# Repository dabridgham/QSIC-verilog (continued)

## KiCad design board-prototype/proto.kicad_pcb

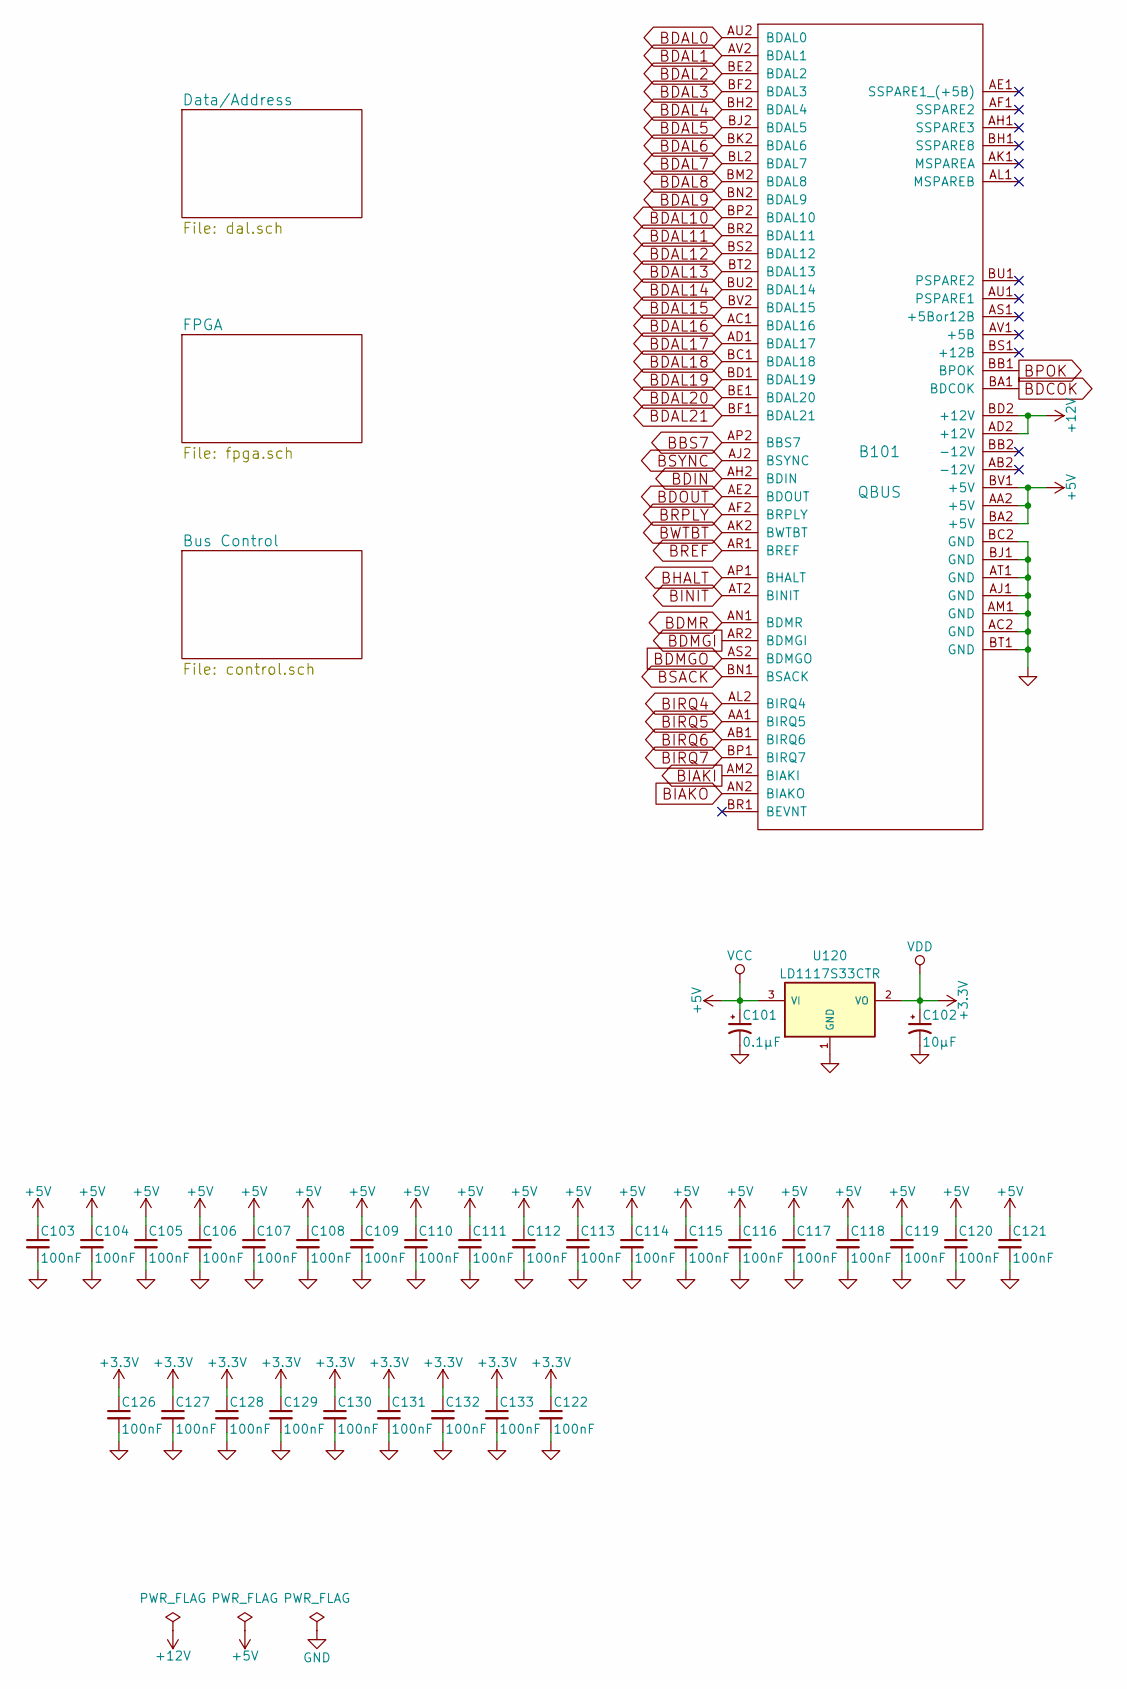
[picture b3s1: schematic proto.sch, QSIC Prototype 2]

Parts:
B101: QBUS; Qbus-double
C101: 0.1µF; TantalC_SizeR_EIA-2012
C102: 10µF; TantalC_SizeR_EIA-2012
C103, C104, C105, C106, C107, C108, C109, C110, C111, C112, C113, C114, C115, C116, C117, C118, C119, C120, C121, C122, C126, C127, C128, C129, C130, C131, C132, C133: 100nF; C_0805
U120: LD1117S33CTR; SOT-223

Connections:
+5V: B101.AA2 (+5V), B101.BA2 (+5V), B101.BV1 (+5V), C101.1, C103.1, C104.1, C105.1, C106.1, C107.1, C108.1, C109.1, C110.1, C111.1, C112.1, C113.1, C114.1, C115.1, C116.1, C117.1, C118.1, C119.1, C120.1, C121.1, U120.3 (VI); also elsewhere on the board
+12V: B101.AD2 (+12V), B101.BD2 (+12V); also elsewhere on the board
BBS7: B101.AP2 (BBS7); also elsewhere on the board
BDAL0: B101.AU2 (BDAL0); also elsewhere on the board
BDAL1: B101.AV2 (BDAL1); also elsewhere on the board
BDAL2: B101.BE2 (BDAL2); also elsewhere on the board
BDAL3: B101.BF2 (BDAL3); also elsewhere on the board
BDAL4: B101.BH2 (BDAL4); also elsewhere on the board
BDAL5: B101.BJ2 (BDAL5); also elsewhere on the board
BDAL6: B101.BK2 (BDAL6); also elsewhere on the board
BDAL7: B101.BL2 (BDAL7); also elsewhere on the board
BDAL8: B101.BM2 (BDAL8); also elsewhere on the board
BDAL9: B101.BN2 (BDAL9); also elsewhere on the board
BDAL10: B101.BP2 (BDAL10); also elsewhere on the board
BDAL11: B101.BR2 (BDAL11); also elsewhere on the board
BDAL12: B101.BS2 (BDAL12); also elsewhere on the board
BDAL13: B101.BT2 (BDAL13); also elsewhere on the board
BDAL14: B101.BU2 (BDAL14); also elsewhere on the board
BDAL15: B101.BV2 (BDAL15); also elsewhere on the board
BDAL16: B101.AC1 (BDAL16); also elsewhere on the board
BDAL17: B101.AD1 (BDAL17); also elsewhere on the board
BDAL18: B101.BC1 (BDAL18); also elsewhere on the board
BDAL19: B101.BD1 (BDAL19); also elsewhere on the board
BDAL20: B101.BE1 (BDAL20); also elsewhere on the board
BDAL21: B101.BF1 (BDAL21); also elsewhere on the board
BDCOK: B101.BA1 (BDCOK); also elsewhere on the board
BDIN: B101.AH2 (BDIN); also elsewhere on the board
BDMGI: B101.AR2 (BDMGI); also elsewhere on the board
BDMGO: B101.AS2 (BDMGO); also elsewhere on the board
BDMR: B101.AN1 (BDMR); also elsewhere on the board
BDOUT: B101.AE2 (BDOUT); also elsewhere on the board
BHALT: B101.AP1 (BHALT); also elsewhere on the board
BIAKI: B101.AM2 (BIAKI); also elsewhere on the board
BIAKO: B101.AN2 (BIAKO); also elsewhere on the board
BINIT: B101.AT2 (BINIT); also elsewhere on the board
BIRQ4: B101.AL2 (BIRQ4); also elsewhere on the board
BIRQ5: B101.AA1 (BIRQ5); also elsewhere on the board
BIRQ6: B101.AB1 (BIRQ6); also elsewhere on the board
BIRQ7: B101.BP1 (BIRQ7); also elsewhere on the board
BPOK: B101.BB1 (BPOK); also elsewhere on the board
BREF: B101.AR1 (BREF); also elsewhere on the board
BRPLY: B101.AF2 (BRPLY); also elsewhere on the board
BSACK: B101.BN1 (BSACK); also elsewhere on the board
BSYNC: B101.AJ2 (BSYNC); also elsewhere on the board
BWTBT: B101.AK2 (BWTBT); also elsewhere on the board

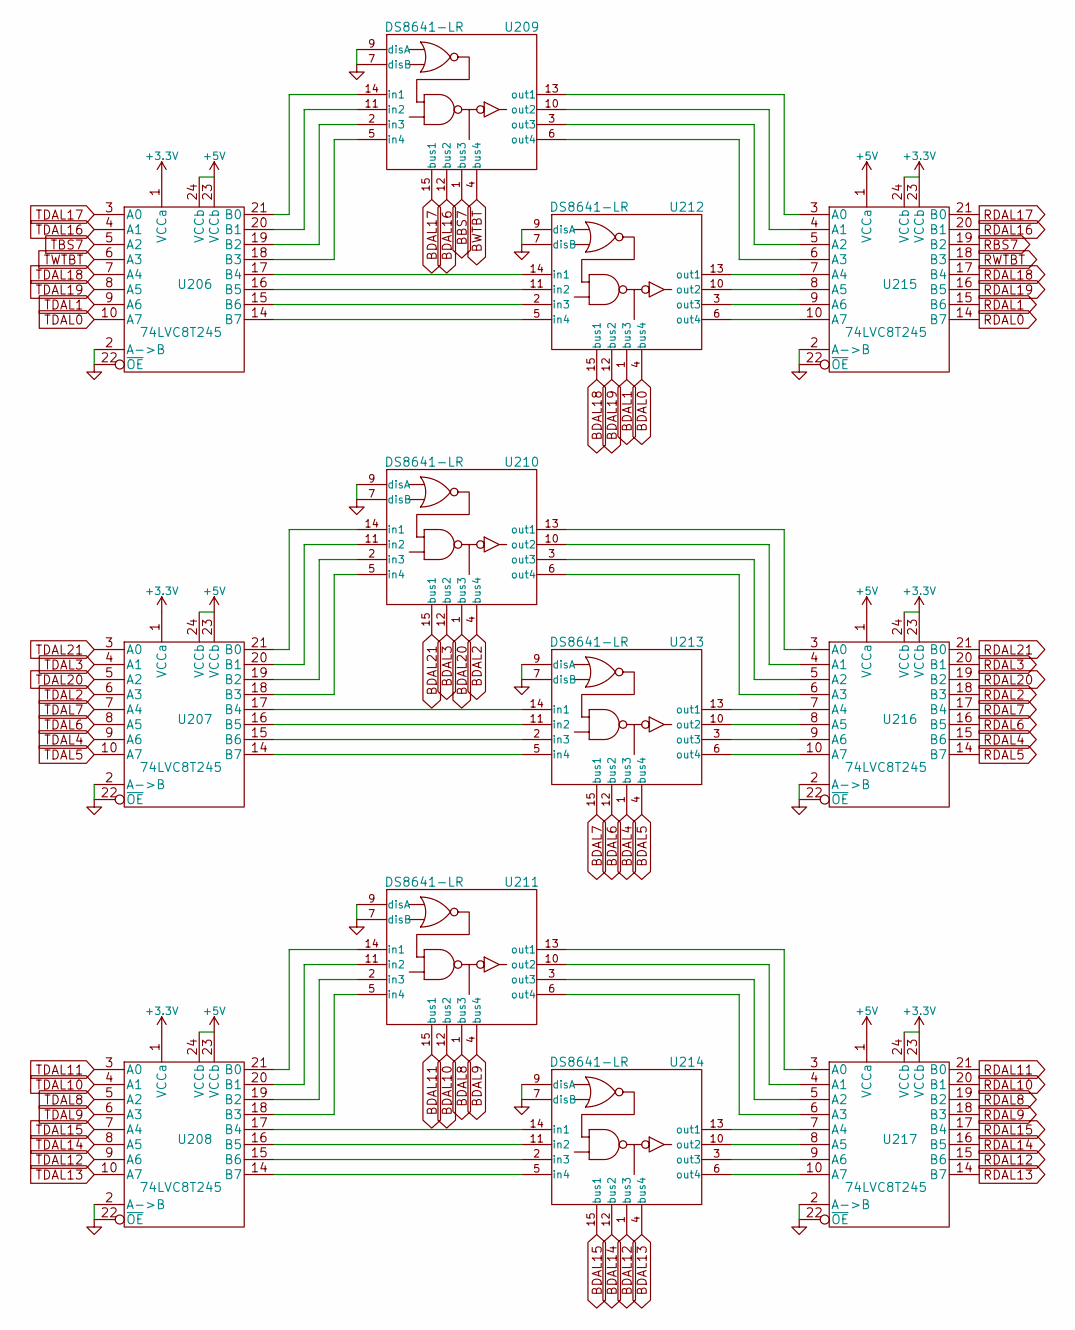
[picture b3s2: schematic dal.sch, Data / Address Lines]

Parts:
U206, U207, U208, U215, U216, U217: 74LVC8T245; TSSOP-24_4.4x7.8mm_Pitch0.65mm
U209, U210, U211, U212, U213, U214: DS8641-LR; DIP-16__300

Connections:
+5V: U206.23 (VCCb), U206.24 (VCCb), U207.23 (VCCb), U207.24 (VCCb), U208.23 (VCCb), U208.24 (VCCb), U209.16 (VCC), U210.16 (VCC), U211.16 (VCC), U212.16 (VCC), U213.16 (VCC), U214.16 (VCC), U215.1 (VCCa), U216.1 (VCCa), U217.1 (VCCa); also elsewhere on the board
BBS7: U209.1 (bus3); also elsewhere on the board
BDAL0: U212.4 (bus4); also elsewhere on the board
BDAL1: U212.1 (bus3); also elsewhere on the board
BDAL2: U210.4 (bus4); also elsewhere on the board
BDAL3: U210.12 (bus2); also elsewhere on the board
BDAL4: U213.1 (bus3); also elsewhere on the board
BDAL5: U213.4 (bus4); also elsewhere on the board
BDAL6: U213.12 (bus2); also elsewhere on the board
BDAL7: U213.15 (bus1); also elsewhere on the board
BDAL8: U211.1 (bus3); also elsewhere on the board
BDAL9: U211.4 (bus4); also elsewhere on the board
BDAL10: U211.12 (bus2); also elsewhere on the board
BDAL11: U211.15 (bus1); also elsewhere on the board
BDAL12: U214.1 (bus3); also elsewhere on the board
BDAL13: U214.4 (bus4); also elsewhere on the board
BDAL14: U214.12 (bus2); also elsewhere on the board
BDAL15: U214.15 (bus1); also elsewhere on the board
BDAL16: U209.12 (bus2); also elsewhere on the board
BDAL17: U209.15 (bus1); also elsewhere on the board
BDAL18: U212.15 (bus1); also elsewhere on the board
BDAL19: U212.12 (bus2); also elsewhere on the board
BDAL20: U210.1 (bus3); also elsewhere on the board
BDAL21: U210.15 (bus1); also elsewhere on the board
BWTBT: U209.4 (bus4); also elsewhere on the board
unnamed: U206.14 (B7), U212.5 (in4)
unnamed: U206.15 (B6), U212.2 (in3)
unnamed: U206.16 (B5), U212.11 (in2)
unnamed: U206.17 (B4), U212.14 (in1)
unnamed: U206.18 (B3), U209.5 (in4)
unnamed: U206.19 (B2), U209.2 (in3)
unnamed: U206.20 (B1), U209.11 (in2)
unnamed: U206.21 (B0), U209.14 (in1)
unnamed: U207.14 (B7), U213.5 (in4)
unnamed: U207.15 (B6), U213.2 (in3)
unnamed: U207.16 (B5), U213.11 (in2)
unnamed: U207.17 (B4), U213.14 (in1)
unnamed: U207.18 (B3), U210.5 (in4)
unnamed: U207.19 (B2), U210.2 (in3)
unnamed: U207.20 (B1), U210.11 (in2)
unnamed: U207.21 (B0), U210.14 (in1)
unnamed: U208.14 (B7), U214.5 (in4)
unnamed: U208.15 (B6), U214.2 (in3)
unnamed: U208.16 (B5), U214.11 (in2)
unnamed: U208.17 (B4), U214.14 (in1)
unnamed: U208.18 (B3), U211.5 (in4)
unnamed: U208.19 (B2), U211.2 (in3)
unnamed: U208.20 (B1), U211.11 (in2)
unnamed: U208.21 (B0), U211.14 (in1)
unnamed: U209.3 (out3), U215.5 (A2)
unnamed: U209.6 (out4), U215.6 (A3)
unnamed: U209.10 (out2), U215.4 (A1)
unnamed: U209.13 (out1), U215.3 (A0)
unnamed: U210.3 (out3), U216.5 (A2)
unnamed: U210.6 (out4), U216.6 (A3)
unnamed: U210.10 (out2), U216.4 (A1)
unnamed: U210.13 (out1), U216.3 (A0)
unnamed: U211.3 (out3), U217.5 (A2)
unnamed: U211.6 (out4), U217.6 (A3)
unnamed: U211.10 (out2), U217.4 (A1)
unnamed: U211.13 (out1), U217.3 (A0)
unnamed: U212.3 (out3), U215.9 (A6)
unnamed: U212.6 (out4), U215.10 (A7)
unnamed: U212.10 (out2), U215.8 (A5)
unnamed: U212.13 (out1), U215.7 (A4)
unnamed: U213.3 (out3), U216.9 (A6)
unnamed: U213.6 (out4), U216.10 (A7)
unnamed: U213.10 (out2), U216.8 (A5)
unnamed: U213.13 (out1), U216.7 (A4)
unnamed: U214.3 (out3), U217.9 (A6)
unnamed: U214.6 (out4), U217.10 (A7)
unnamed: U214.10 (out2), U217.8 (A5)
unnamed: U214.13 (out1), U217.7 (A4)
RBS7: U215.19 (B2); also elsewhere on the board
RDAL0: U215.14 (B7); also elsewhere on the board
RDAL1: U215.15 (B6); also elsewhere on the board
RDAL2: U216.18 (B3); also elsewhere on the board
RDAL3: U216.20 (B1); also elsewhere on the board
RDAL4: U216.15 (B6); also elsewhere on the board
RDAL5: U216.14 (B7); also elsewhere on the board
RDAL6: U216.16 (B5); also elsewhere on the board
RDAL7: U216.17 (B4); also elsewhere on the board
RDAL8: U217.19 (B2); also elsewhere on the board
RDAL9: U217.18 (B3); also elsewhere on the board
RDAL10: U217.20 (B1); also elsewhere on the board
RDAL11: U217.21 (B0); also elsewhere on the board
RDAL12: U217.15 (B6); also elsewhere on the board
RDAL13: U217.14 (B7); also elsewhere on the board
RDAL14: U217.16 (B5); also elsewhere on the board
RDAL15: U217.17 (B4); also elsewhere on the board
RDAL16: U215.20 (B1); also elsewhere on the board
RDAL17: U215.21 (B0); also elsewhere on the board
RDAL18: U215.17 (B4); also elsewhere on the board
RDAL19: U215.16 (B5); also elsewhere on the board
RDAL20: U216.19 (B2); also elsewhere on the board
RDAL21: U216.21 (B0); also elsewhere on the board
RWTBT: U215.18 (B3); also elsewhere on the board
TBS7: U206.5 (A2); also elsewhere on the board
TDAL0: U206.10 (A7); also elsewhere on the board
TDAL1: U206.9 (A6); also elsewhere on the board
TDAL2: U207.6 (A3); also elsewhere on the board
TDAL3: U207.4 (A1); also elsewhere on the board
TDAL4: U207.9 (A6); also elsewhere on the board
TDAL5: U207.10 (A7); also elsewhere on the board
TDAL6: U207.8 (A5); also elsewhere on the board
TDAL7: U207.7 (A4); also elsewhere on the board
TDAL8: U208.5 (A2); also elsewhere on the board
TDAL9: U208.6 (A3); also elsewhere on the board
TDAL10: U208.4 (A1); also elsewhere on the board
TDAL11: U208.3 (A0); also elsewhere on the board
TDAL12: U208.9 (A6); also elsewhere on the board
TDAL13: U208.10 (A7); also elsewhere on the board
TDAL14: U208.8 (A5); also elsewhere on the board
TDAL15: U208.7 (A4); also elsewhere on the board
TDAL16: U206.4 (A1); also elsewhere on the board
TDAL17: U206.3 (A0); also elsewhere on the board
TDAL18: U206.7 (A4); also elsewhere on the board
TDAL19: U206.8 (A5); also elsewhere on the board
TDAL20: U207.5 (A2); also elsewhere on the board
TDAL21: U207.3 (A0); also elsewhere on the board
TWTBT: U206.6 (A3); also elsewhere on the board

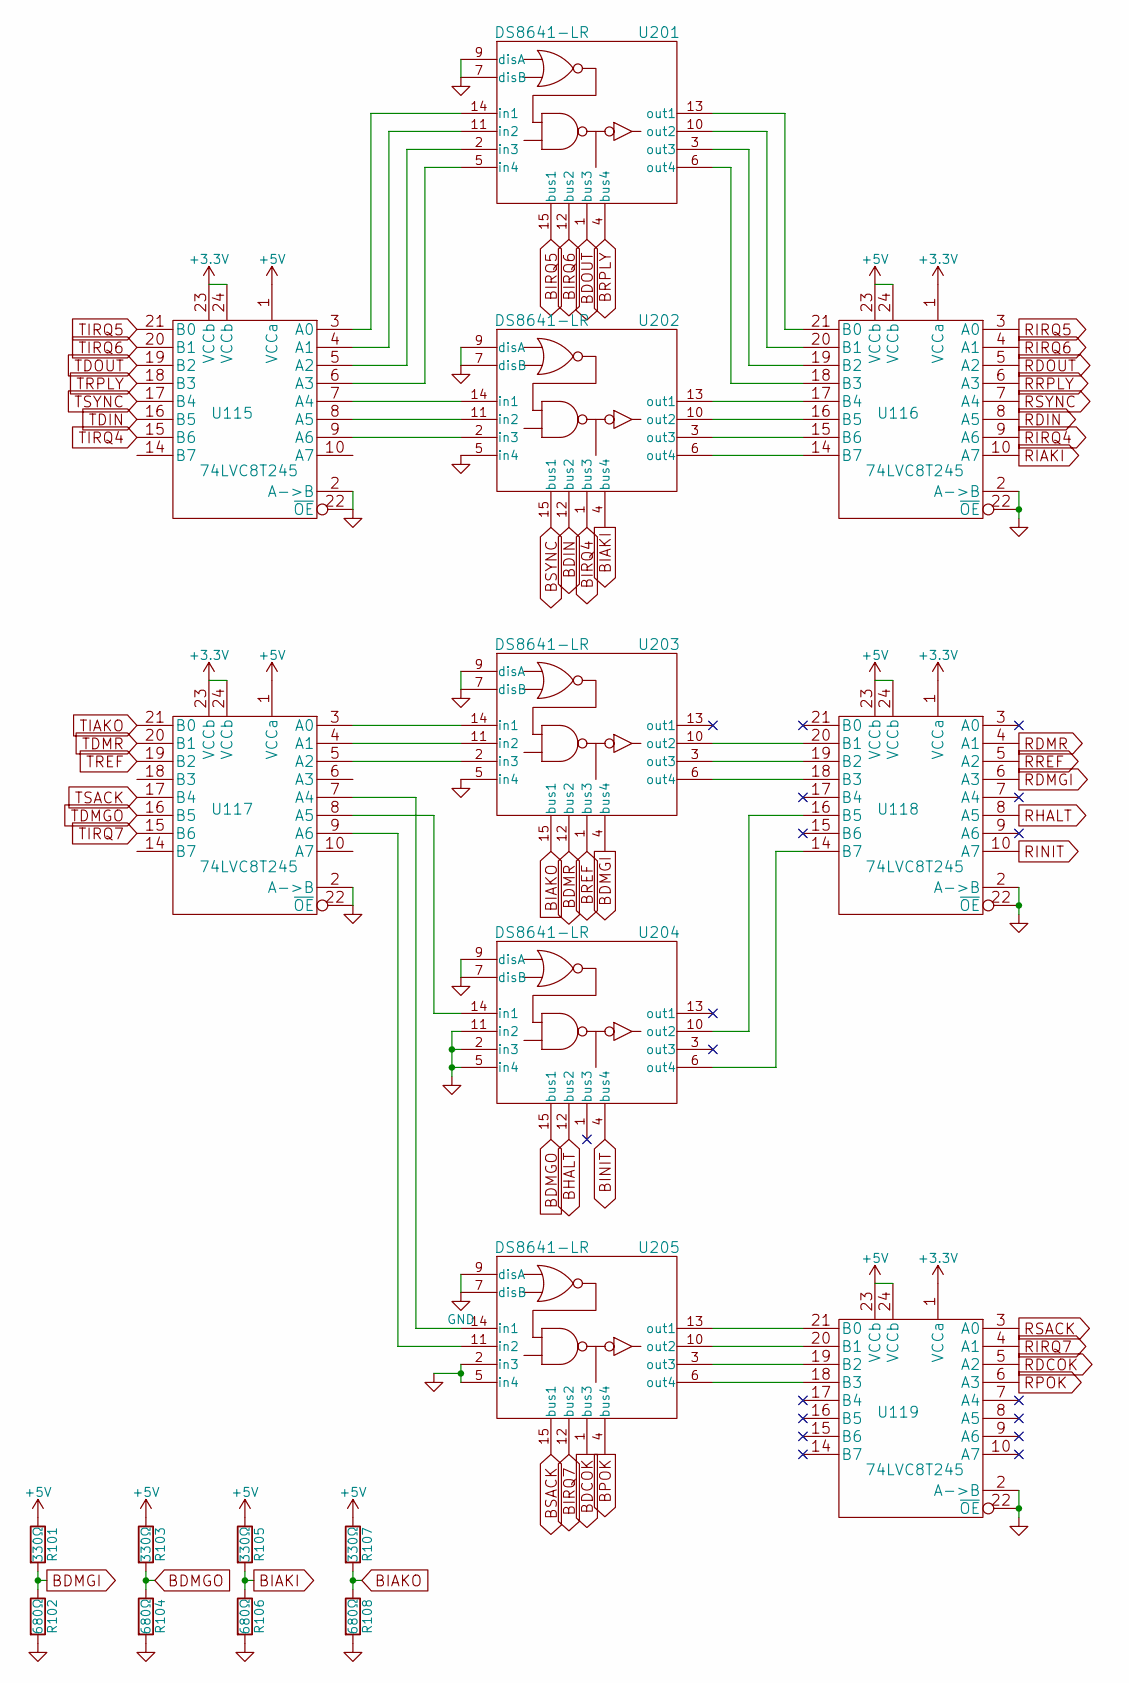
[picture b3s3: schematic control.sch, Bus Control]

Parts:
R101, R103, R105, R107: 330Ω; R_0805
R102, R104, R106, R108: 680Ω; R_0805
U115, U116, U117, U118, U119: 74LVC8T245; TSSOP-24_4.4x7.8mm_Pitch0.65mm
U201, U202, U203, U204, U205: DS8641-LR; DIP-16__300

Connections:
+5V: R101.1, R103.1, R105.1, R107.1, U115.1 (VCCa), U116.23 (VCCb), U116.24 (VCCb), U117.1 (VCCa), U118.23 (VCCb), U118.24 (VCCb), U119.23 (VCCb), U119.24 (VCCb), U201.16 (VCC), U202.16 (VCC), U203.16 (VCC), U204.16 (VCC), U205.16 (VCC); also elsewhere on the board
BDCOK: U205.1 (bus3); also elsewhere on the board
BDIN: U202.12 (bus2); also elsewhere on the board
BDMGI: R101.2, R102.1, U203.4 (bus4); also elsewhere on the board
BDMGO: R103.2, R104.1, U204.15 (bus1); also elsewhere on the board
BDMR: U203.12 (bus2); also elsewhere on the board
BDOUT: U201.1 (bus3); also elsewhere on the board
BHALT: U204.12 (bus2); also elsewhere on the board
BIAKI: R105.2, R106.1, U202.4 (bus4); also elsewhere on the board
BIAKO: R107.2, R108.1, U203.15 (bus1); also elsewhere on the board
BINIT: U204.4 (bus4); also elsewhere on the board
BIRQ4: U202.1 (bus3); also elsewhere on the board
BIRQ5: U201.15 (bus1); also elsewhere on the board
BIRQ6: U201.12 (bus2); also elsewhere on the board
BIRQ7: U205.12 (bus2); also elsewhere on the board
BPOK: U205.4 (bus4); also elsewhere on the board
BREF: U203.1 (bus3); also elsewhere on the board
BRPLY: U201.4 (bus4); also elsewhere on the board
BSACK: U205.15 (bus1); also elsewhere on the board
BSYNC: U202.15 (bus1); also elsewhere on the board
unnamed: U115.3 (A0), U201.14 (in1)
unnamed: U115.4 (A1), U201.11 (in2)
unnamed: U115.5 (A2), U201.2 (in3)
unnamed: U115.6 (A3), U201.5 (in4)
unnamed: U115.7 (A4), U202.14 (in1)
unnamed: U115.8 (A5), U202.11 (in2)
unnamed: U115.9 (A6), U202.2 (in3)
unnamed: U116.14 (B7), U202.6 (out4)
unnamed: U116.15 (B6), U202.3 (out3)
unnamed: U116.16 (B5), U202.10 (out2)
unnamed: U116.17 (B4), U202.13 (out1)
unnamed: U116.18 (B3), U201.6 (out4)
unnamed: U116.19 (B2), U201.3 (out3)
unnamed: U116.20 (B1), U201.10 (out2)
unnamed: U116.21 (B0), U201.13 (out1)
unnamed: U117.3 (A0), U203.14 (in1)
unnamed: U117.4 (A1), U203.11 (in2)
unnamed: U117.5 (A2), U203.2 (in3)
unnamed: U117.8 (A5), U204.14 (in1)
unnamed: U118.14 (B7), U204.6 (out4)
unnamed: U118.16 (B5), U204.10 (out2)
unnamed: U118.18 (B3), U203.6 (out4)
unnamed: U118.19 (B2), U203.3 (out3)
unnamed: U118.20 (B1), U203.10 (out2)
unnamed: U119.18 (B3), U205.6 (out4)
unnamed: U119.19 (B2), U205.3 (out3)
unnamed: U119.20 (B1), U205.10 (out2)
unnamed: U119.21 (B0), U205.13 (out1)
RDIN: U116.8 (A5); also elsewhere on the board
RDMGI: U118.6 (A3); also elsewhere on the board
RDMR: U118.4 (A1); also elsewhere on the board
RDOUT: U116.5 (A2); also elsewhere on the board
RHALT: U118.8 (A5); also elsewhere on the board
RIAKI: U116.10 (A7); also elsewhere on the board
RINIT: U118.10 (A7); also elsewhere on the board
RIRQ4: U116.9 (A6); also elsewhere on the board
RIRQ5: U116.3 (A0); also elsewhere on the board
RIRQ6: U116.4 (A1); also elsewhere on the board
RREF: U118.5 (A2); also elsewhere on the board
RRPLY: U116.6 (A3); also elsewhere on the board
RSYNC: U116.7 (A4); also elsewhere on the board
TDIN: U115.16 (B5); also elsewhere on the board
TDMGO: U117.16 (B5); also elsewhere on the board
TDMR: U117.20 (B1); also elsewhere on the board
TDOUT: U115.19 (B2); also elsewhere on the board
TIAKO: U117.21 (B0); also elsewhere on the board
TIRQ4: U115.15 (B6); also elsewhere on the board
TIRQ5: U115.21 (B0); also elsewhere on the board
TIRQ6: U115.20 (B1); also elsewhere on the board
TIRQ7: U115.14 (B7); also elsewhere on the board
TREF: U117.19 (B2); also elsewhere on the board
TRPLY: U115.18 (B3); also elsewhere on the board
TSACK: U117.17 (B4); also elsewhere on the board
TSYNC: U115.17 (B4); also elsewhere on the board

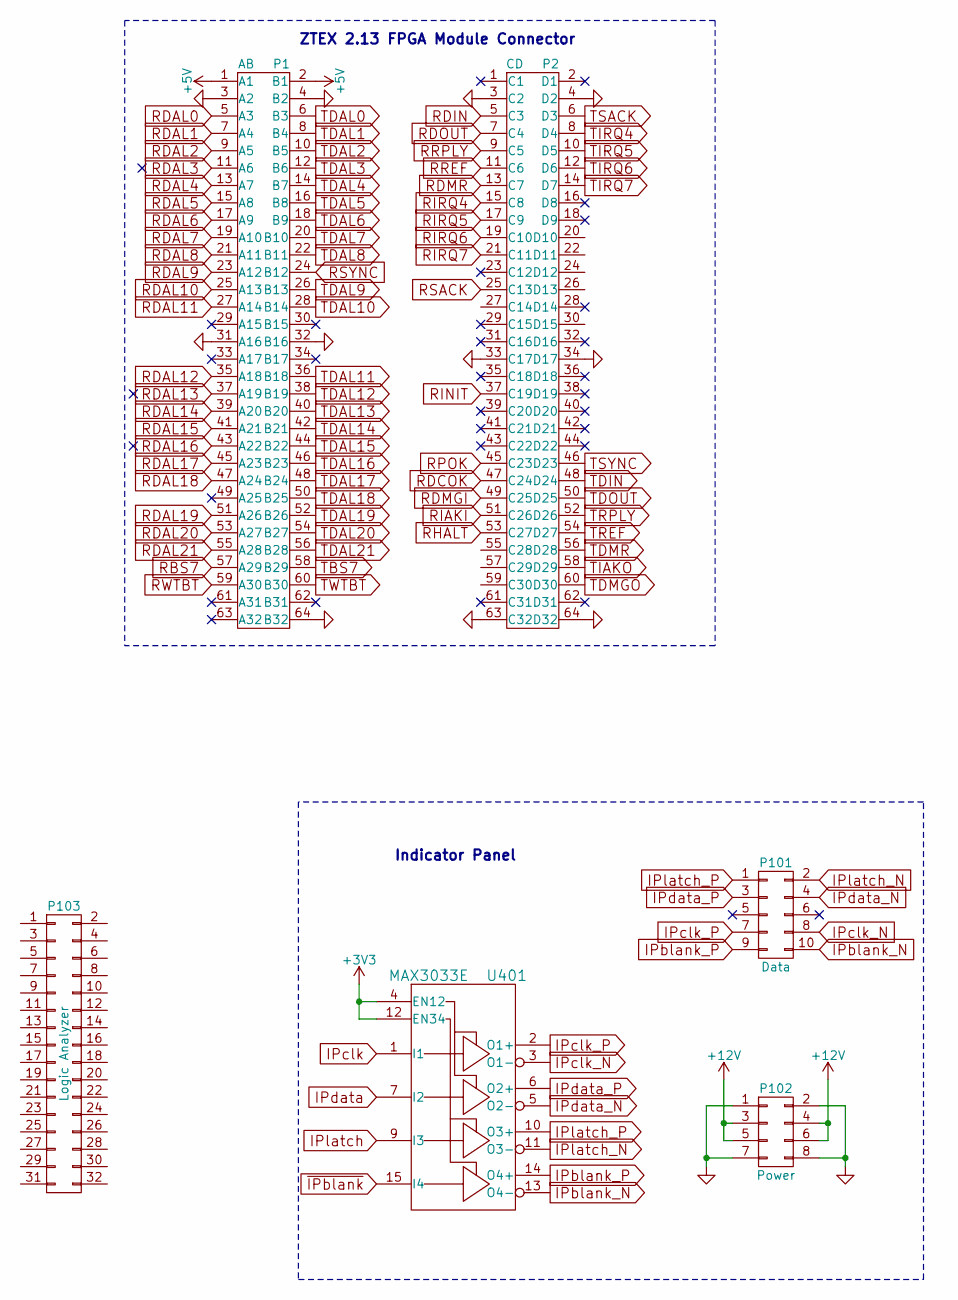
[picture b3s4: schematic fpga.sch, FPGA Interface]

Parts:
P1: AB; Pin_Header_Straight_2x32
P2: CD; Pin_Header_Straight_2x32
P101: Data; Pin_Header_Angled_2x05
P102: Power; Pin_Header_Angled_2x04
P103: Logic Analyzer; Pin_Header_Straight_2x16
U401: MAX3033E; SOIC-16_3.9x9.9mm_Pitch1.27mm

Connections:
+5V: P1.1 (A1), P1.2 (B1); also elsewhere on the board
+12V: P102.3, P102.4, P102.5, P102.6; also elsewhere on the board
IPblank_N: P101.10, U401.13 (O4-)
IPblank_P: P101.9, U401.14 (O4+)
IPclk: U401.1 (I1)
IPclk_N: P101.8, U401.3 (O1-)
IPclk_P: P101.7, U401.2 (O1+)
IPdata: U401.7 (I2)
IPdata_N: P101.4, U401.5 (O2-)
IPdata_P: P101.3, U401.6 (O2+)
IPlatch: U401.9 (I3)
IPlatch_N: P101.2, U401.11 (O3-)
IPlatch_P: P101.1, U401.10 (O3+)
RBS7: P1.57 (A29); also elsewhere on the board
RDAL0: P1.5 (A3); also elsewhere on the board
RDAL1: P1.7 (A4); also elsewhere on the board
RDAL2: P1.9 (A5); also elsewhere on the board
RDAL3: P1.11 (A6); also elsewhere on the board
RDAL4: P1.13 (A7); also elsewhere on the board
RDAL5: P1.15 (A8); also elsewhere on the board
RDAL6: P1.17 (A9); also elsewhere on the board
RDAL7: P1.19 (A10); also elsewhere on the board
RDAL8: P1.21 (A11); also elsewhere on the board
RDAL9: P1.23 (A12); also elsewhere on the board
RDAL10: P1.25 (A13); also elsewhere on the board
RDAL11: P1.27 (A14); also elsewhere on the board
RDAL12: P1.35 (A18); also elsewhere on the board
RDAL13: P1.37 (A19); also elsewhere on the board
RDAL14: P1.39 (A20); also elsewhere on the board
RDAL15: P1.41 (A21); also elsewhere on the board
RDAL16: P1.43 (A22); also elsewhere on the board
RDAL17: P1.45 (A23); also elsewhere on the board
RDAL18: P1.47 (A24); also elsewhere on the board
RDAL19: P1.51 (A26); also elsewhere on the board
RDAL20: P1.53 (A27); also elsewhere on the board
RDAL21: P1.55 (A28); also elsewhere on the board
RDIN: P2.5 (C3); also elsewhere on the board
RDMGI: P2.49 (C25); also elsewhere on the board
RDMR: P2.13 (C7); also elsewhere on the board
RDOUT: P2.7 (C4); also elsewhere on the board
RHALT: P2.53 (C27); also elsewhere on the board
RIAKI: P2.51 (C26); also elsewhere on the board
RINIT: P2.37 (C19); also elsewhere on the board
RIRQ4: P2.15 (C8); also elsewhere on the board
RIRQ5: P2.17 (C9); also elsewhere on the board
RIRQ6: P2.19 (C10); also elsewhere on the board
RREF: P2.11 (C6); also elsewhere on the board
RRPLY: P2.9 (C5); also elsewhere on the board
RSYNC: P1.24 (B12); also elsewhere on the board
RWTBT: P1.59 (A30); also elsewhere on the board
TBS7: P1.58 (B29); also elsewhere on the board
TDAL0: P1.6 (B3); also elsewhere on the board
TDAL1: P1.8 (B4); also elsewhere on the board
TDAL2: P1.10 (B5); also elsewhere on the board
TDAL3: P1.12 (B6); also elsewhere on the board
TDAL4: P1.14 (B7); also elsewhere on the board
TDAL5: P1.16 (B8); also elsewhere on the board
TDAL6: P1.18 (B9); also elsewhere on the board
TDAL7: P1.20 (B10); also elsewhere on the board
TDAL8: P1.22 (B11); also elsewhere on the board
TDAL9: P1.26 (B13); also elsewhere on the board
TDAL10: P1.28 (B14); also elsewhere on the board
TDAL11: P1.36 (B18); also elsewhere on the board
TDAL12: P1.38 (B19); also elsewhere on the board
TDAL13: P1.40 (B20); also elsewhere on the board
TDAL14: P1.42 (B21); also elsewhere on the board
TDAL15: P1.44 (B22); also elsewhere on the board
TDAL16: P1.46 (B23); also elsewhere on the board
TDAL17: P1.48 (B24); also elsewhere on the board
TDAL18: P1.50 (B25); also elsewhere on the board
TDAL19: P1.52 (B26); also elsewhere on the board
TDAL20: P1.54 (B27); also elsewhere on the board
TDAL21: P1.56 (B28); also elsewhere on the board
TDIN: P2.48 (D24); also elsewhere on the board
TDMGO: P2.60 (D30); also elsewhere on the board
TDMR: P2.56 (D28); also elsewhere on the board
TDOUT: P2.50 (D25); also elsewhere on the board
TIAKO: P2.58 (D29); also elsewhere on the board
TIRQ4: P2.8 (D4); also elsewhere on the board
TIRQ5: P2.10 (D5); also elsewhere on the board
TIRQ6: P2.12 (D6); also elsewhere on the board
TIRQ7: P2.14 (D7); also elsewhere on the board
TREF: P2.54 (D27); also elsewhere on the board
TRPLY: P2.52 (D26); also elsewhere on the board
TSACK: P2.6 (D3); also elsewhere on the board
TSYNC: P2.46 (D23); also elsewhere on the board
TWTBT: P1.60 (B30); also elsewhere on the board
~IPblank: U401.15 (I4)

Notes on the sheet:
ZTEX 2.13 FPGA Module Connector
Indicator Panel

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
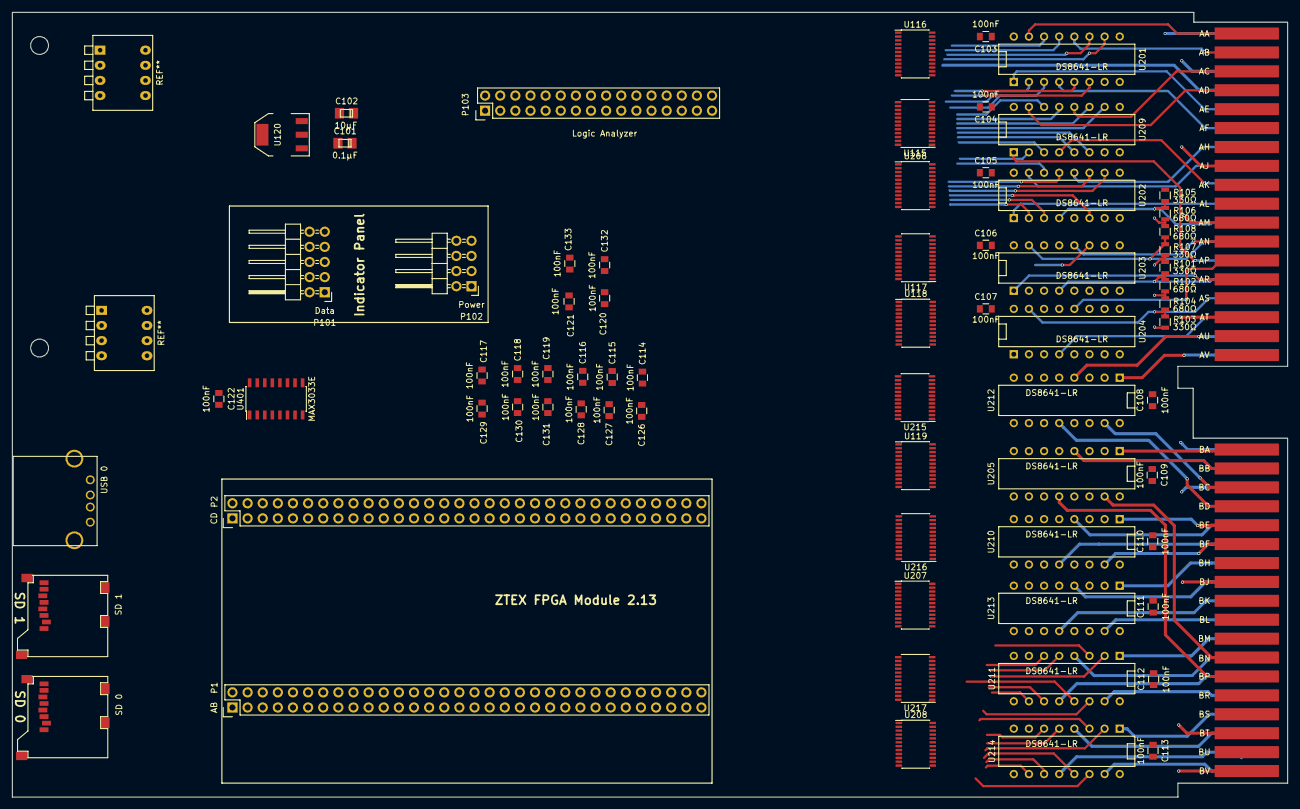
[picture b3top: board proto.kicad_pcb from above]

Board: 4 copper layers, 214.1 x 131.7 mm, 73 parts (0 on the bottom side), 211 nets.

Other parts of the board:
SD 0, SD 1: microSD 3M; microSD-3M-2900-series
USB 0: USB_A
h1, h2: MountingHole_3mm
